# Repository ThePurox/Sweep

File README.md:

# Sweep
<!--
           ___                        ___
      ___ |   | ___ ___      ___ ___ |   | ___
 ___ |   |`___`|   |   |    |   |   |`___`|   | ___
|   |`___`|   |`___`___`    `___`___`|   |`___`|   |
`___`|   |`___`|   |   |    |   |   |`___`|   |`___`
|   |`___`|   |`___`___`    `___`___`|   |`___`|   |
`___`|   |`___`|   |   |    |   |   |`___`|   |`___`
|   |`___`     `___`___`    `___`___`     `___`|   |
`___`           ___ ___      ___ ___           `___`
               |   |   |    |   |   |
               `___`___`    `___`___`
-->
>    
> <sub>Bluetooth Sweep 2 + MBK Legend Keycaps</sub>

<span>

</span>

## What is sweep?

Sweep is a version of the more fabulous [Ferris](https://github.com/pierrechevalier83/ferris) by [Pierre Chevalier](https://github.com/pierrechevalier83/) that uses a daughter board like a promicro, elite-c, bit-c, nice!nano etc. instead of using onboard components.

## What are the different types?

⭐ Sweep 2 - Recommended Choc v1 board with all the features.  
⭕ Sweep Half Swept - Same as Sweep 2, but with a reversible pro-micro footprint.  
⭕ Sweep Bling MX - An MX only Sweep that features Kailh's hotswap sockets and a stacked case.  
⭕ Sweep Bling LP - A Choc v1 only Sweep that features Kailh's hotswap sockets.  
⭕ Sweep High - Same as the Sweep 2, but trades choc spacing for compatibility with more switches and keycaps.  
⭕ Sweep High M - A soldered MX only Sweep, with a reversible PCB design.  
⭕ Sweep Mini - The only version that supports Choc minis.  
⭕ Sweep ULP - A version for the Cherry Ultra low profile switches.  

| Device | On/Off Switch<sup>[1]</sup> | Reversible PCB<sup>[2]</sup> | Choc V1 | Choc V2 | Choc Mini | MX & Alps | Cherry ULP | Choc Spacing<sup>[3]</sup> | Tenting<sup>[4]</sup> | Hot Swap |
| :--- | :---: | :---: | :---: | :---: | :---: | :---: | :---: | :---: | :---: | :---: |
| Sweep2.x          | ✔ |   | ✔ |   |   |   |   | ✔ | ✔ | Mill-Max (optional) |
| Sweep Bling LP    | ✔ |   | ✔ |   |   |   |   | ✔ | ✔ | Kailh (required) |
| Sweep Bling MX    | ✔ | ✔ |   |   |   | ⚠<br/><sup>[5]</sup> |   |   | ✔ | Kailh (required) |
| Sweep High        | ✔ |   | ✔ | ✔ |   | ✔ |   |   | ✔ |
| Sweep High M      | ✔ | ✔ |   |   |   | MX|   |   | ✔ |   |
| Sweep Half Swept  | ✔ | ✔ | ✔ |   |   |   |   | ✔ | ✔ | Mill-Max (optional) |
| Sweep Mini        |   | ✔ |   |   | ✔ |   |   | ✔ |   |
| Sweep ULP         | ✔ |   |   |   |   |   | ✔ | ✔ |   |

> Note: All versions support bluetooth with Nice!Nano

*<sup>[1]</sup> An on/off switch is recommended for bluetooth builds.*  
*<sup>[2]</sup> With a reversible PCB it's easier to make mistakes during assembly, but it allows you to purchase less boards.*  
*<sup>[3]</sup> Choc spaced boards have the switches in a tighter grid. This provides a better final look but is only compatible with some choc keycaps. (e.g. MBK)*  
*<sup>[4]</sup> Supports splitkb's [tenting puck.](https://splitkb.com/products/tenting-puck?_pos=1&_psq=tenting%20&_ss=e&_v=1.0)*  
*<sup>[5]</sup> MX + kailh hotswap ONLY. Alps are NOT supported.*  

## Components list

To build and use a Sweep you will need:

* 1x PCB Kit
* 2x promicro compatible boards or 2 nice!nanos.
* 34 switches of a compatible type (refer to the compatibility table)
* 34 keycaps
* 2x reset switches (optional; [B3U-1000P(M)](https://github.com/davidphilipbarr/Sweep/issues/20))
* Some little rubber feet/bumpers
* 2x power switches (optional if supported; MSK 12C02)
* 1x TRRS (not TRS!) cable (wired build only)
* 2x TRRS Jack [PJ-320A] (wired build only)
* 1 USB Cable (depends on your micro-controller choice)

## How do I make this thing?

## Firmware

The firmware can be found [with the Ferris  firmware as part of QMK](https://github.com/qmk/qmk_firmware/tree/master/keyboards/ferris/sweep).

Firmware for zmk and bluemicro_ble is called ["Cradio"](https://zmk.dev/docs/hardware/).

## Who made this?

* [Pierre Chevalier](https://github.com/pierrechevalier83)
* [David Barr](https://github.com/davidphilipbarr)
* [Ibnu Daru Aji](https://github.com/ibnuda/)
* [Duccio](https://github.com/duckyb)

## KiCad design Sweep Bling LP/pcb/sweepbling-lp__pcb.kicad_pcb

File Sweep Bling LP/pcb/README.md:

# Sweep Bling LP

This is a kailh hotswap version of the Sweep v2.

This is for choc V2 not compatible with choc v1!!!

## Ordering The PCB

To order the PCB the following settings are recommended<sup>1,2</sup>: 

|Detail|Value|
|---|---|
|Gerber file|`sweepbling-lp__pcb-gerber.zip`|
|Base material|FR-4|
|Layers|2|
|Dimension|216.9mm x 86.9mm|
|Different design|2|
|Delivery format|Panel by customer|
|PCB thickness|1.6mm|
|PCB color|(Personal preference)|
|Silkscreen|(Personal preference)|
|Surface finish|(Personal preference)|
|Outer copper weight|1oz|
|Gold Fingers|No|
|Confirm production file|No|
|Castellated holes|No|
|Remove order number|Yes|

1: Settings are for [JLCPCB](https://jlcpcb.com/), but could work for other manufacturers.

2: Settings are taken from [Kyek's video guide](https://www.youtube.com/watch?v=fBPu7AyDtkM&t=17s).

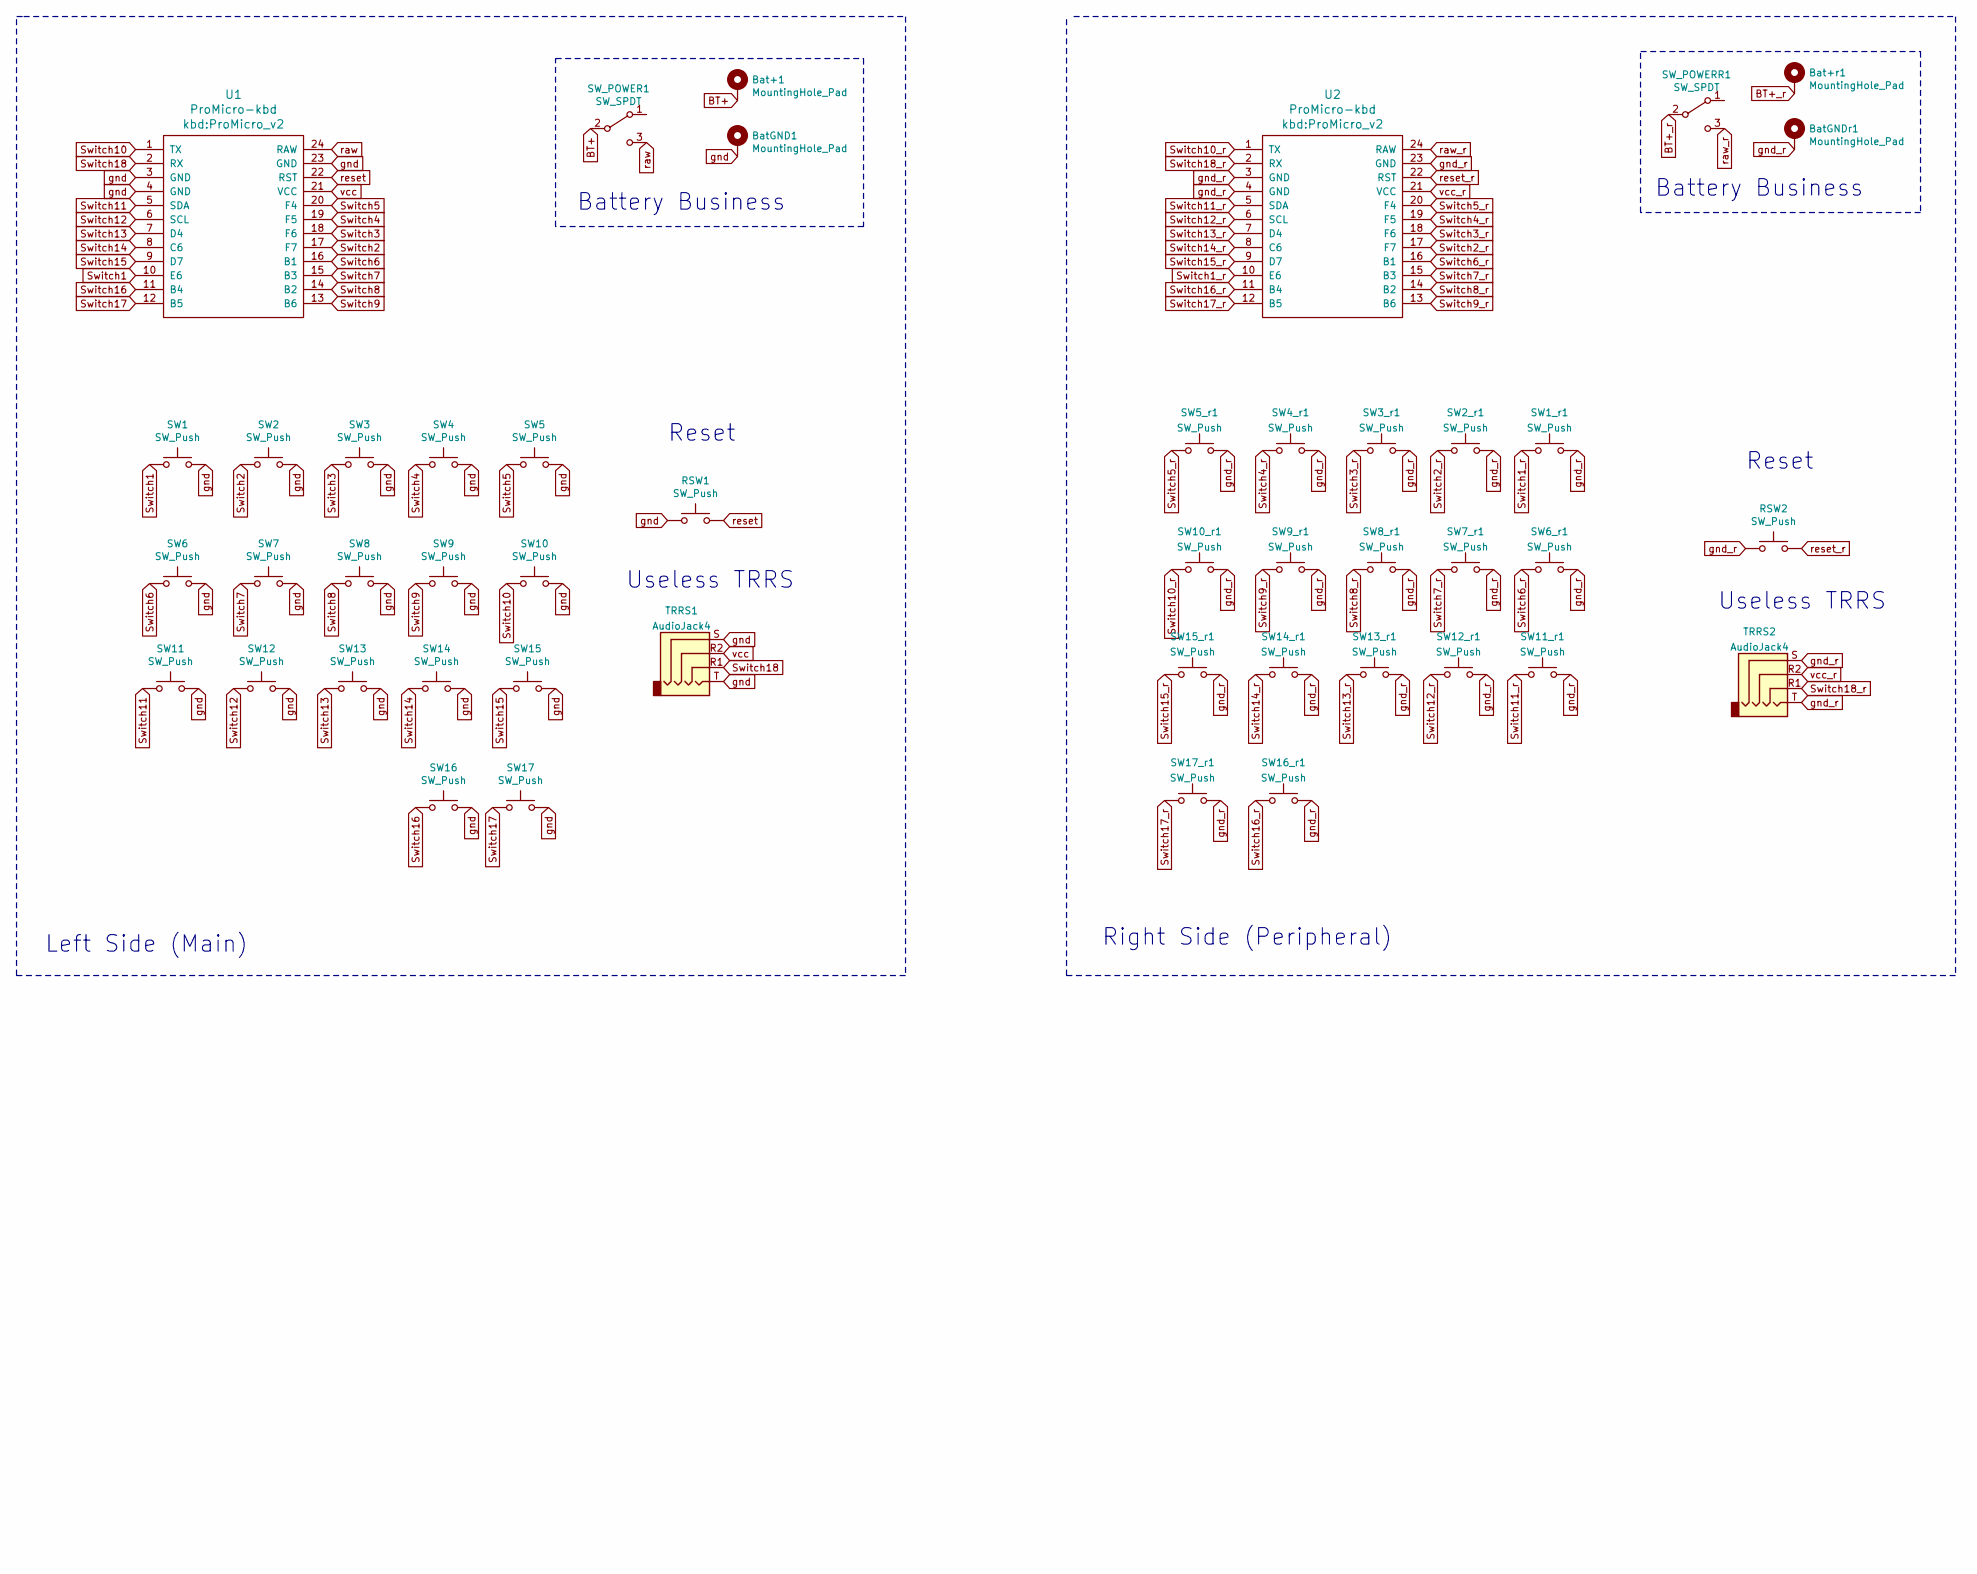
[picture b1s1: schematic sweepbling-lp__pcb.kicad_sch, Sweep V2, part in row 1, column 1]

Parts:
Bat+1: MountingHole_Pad; 1pin_conn
Bat+r1: MountingHole_Pad; 1pin_conn
BatGND1: MountingHole_Pad; 1pin_conn
BatGNDr1: MountingHole_Pad; 1pin_conn
RSW1, RSW2: SW_Push; ResetSW
SW1, SW1_r1, SW2, SW2_r1, SW3, SW3_r1, SW4, SW4_r1, SW5, SW5_r1, SW6, SW6_r1, SW7, SW7_r1, SW8, SW8_r1, SW9, SW9_r1, SW10, SW10_r1, SW11, SW11_r1, SW12, SW12_r1, SW13, SW13_r1, SW14, SW14_r1, SW15, SW15_r1, SW16, SW16_r1, SW17, SW17_r1: SW_Push; SW_PG1350_rev_DPB
SW_POWER1: SW_SPDT; SPDT_C128955
SW_POWERR1: SW_SPDT; SPDT_C128955
TRRS1, TRRS2: AudioJack4
U1, U2: ProMicro-kbd; ProMicro_v2

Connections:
BT+: Bat+1.1 (1_1), SW_POWER1.2 (B)
BT+_r: Bat+r1.1 (1_1), SW_POWERR1.2 (B)
Switch1: SW1.2, U1.10 (E6)
Switch1_r: SW1_r1.2, U2.10 (E6)
Switch2: SW2.2, U1.17 (F7)
Switch2_r: SW2_r1.2, U2.17 (F7)
Switch3: SW3.2, U1.18 (F6)
Switch3_r: SW3_r1.2, U2.18 (F6)
Switch4: SW4.2, U1.19 (F5)
Switch4_r: SW4_r1.2, U2.19 (F5)
Switch5: SW5.2, U1.20 (F4)
Switch5_r: SW5_r1.2, U2.20 (F4)
Switch6: SW6.2, U1.16 (B1)
Switch6_r: SW6_r1.2, U2.16 (B1)
Switch7: SW7.2, U1.15 (B3)
Switch7_r: SW7_r1.2, U2.15 (B3)
Switch8: SW8.2, U1.14 (B2)
Switch8_r: SW8_r1.2, U2.14 (B2)
Switch9: SW9.2, U1.13 (B6)
Switch9_r: SW9_r1.2, U2.13 (B6)
Switch10: SW10.2, U1.1 (TX)
Switch10_r: SW10_r1.2, U2.1 (TX)
Switch11: SW11.2, U1.5 (SDA)
Switch11_r: SW11_r1.2, U2.5 (SDA)
Switch12: SW12.2, U1.6 (SCL)
Switch12_r: SW12_r1.2, U2.6 (SCL)
Switch13: SW13.2, U1.7 (D4)
Switch13_r: SW13_r1.2, U2.7 (D4)
Switch14: SW14.2, U1.8 (C6)
Switch14_r: SW14_r1.2, U2.8 (C6)
Switch15: SW15.2, U1.9 (D7)
Switch15_r: SW15_r1.2, U2.9 (D7)
Switch16: SW16.2, U1.11 (B4)
Switch16_r: SW16_r1.2, U2.11 (B4)
Switch17: SW17.2, U1.12 (B5)
Switch17_r: SW17_r1.2, U2.12 (B5)
Switch18: TRRS1.R1, U1.2 (RX)
Switch18_r: TRRS2.R1, U2.2 (RX)
gnd: BatGND1.1 (1_1), RSW1.1, SW1.1, SW2.1, SW3.1, SW4.1, SW5.1, SW6.1, SW7.1, SW8.1, SW9.1, SW10.1, SW11.1, SW12.1, SW13.1, SW14.1, SW15.1, SW16.1, SW17.1, TRRS1.S, TRRS1.T, U1.3 (GND), U1.4 (GND), U1.23 (GND)
gnd_r: BatGNDr1.1 (1_1), RSW2.1, SW1_r1.1, SW2_r1.1, SW3_r1.1, SW4_r1.1, SW5_r1.1, SW6_r1.1, SW7_r1.1, SW8_r1.1, SW9_r1.1, SW10_r1.1, SW11_r1.1, SW12_r1.1, SW13_r1.1, SW14_r1.1, SW15_r1.1, SW16_r1.1, SW17_r1.1, TRRS2.S, TRRS2.T, U2.3 (GND), U2.4 (GND), U2.23 (GND)
raw: SW_POWER1.3 (C), U1.24 (RAW)
raw_r: SW_POWERR1.3 (C), U2.24 (RAW)
reset: RSW1.2, U1.22 (RST)
reset_r: RSW2.2, U2.22 (RST)
vcc: TRRS1.R2, U1.21 (VCC)
vcc_r: TRRS2.R2, U2.21 (VCC)

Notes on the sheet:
Battery Business
Useless TRRS
Reset
Left Side (Main)
Right Side (Peripheral)

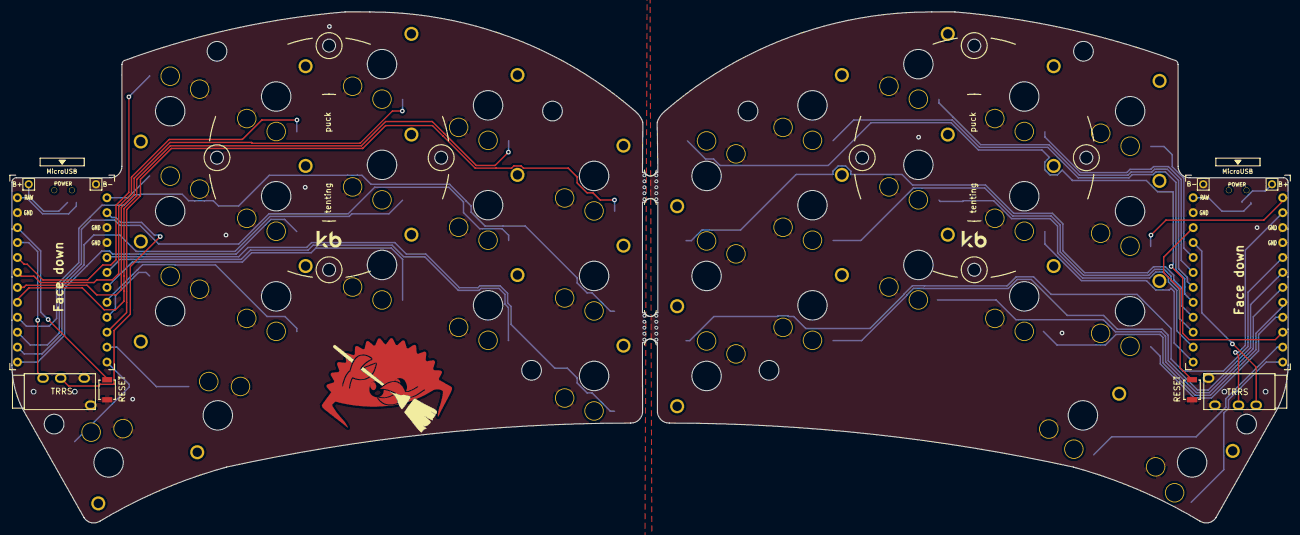
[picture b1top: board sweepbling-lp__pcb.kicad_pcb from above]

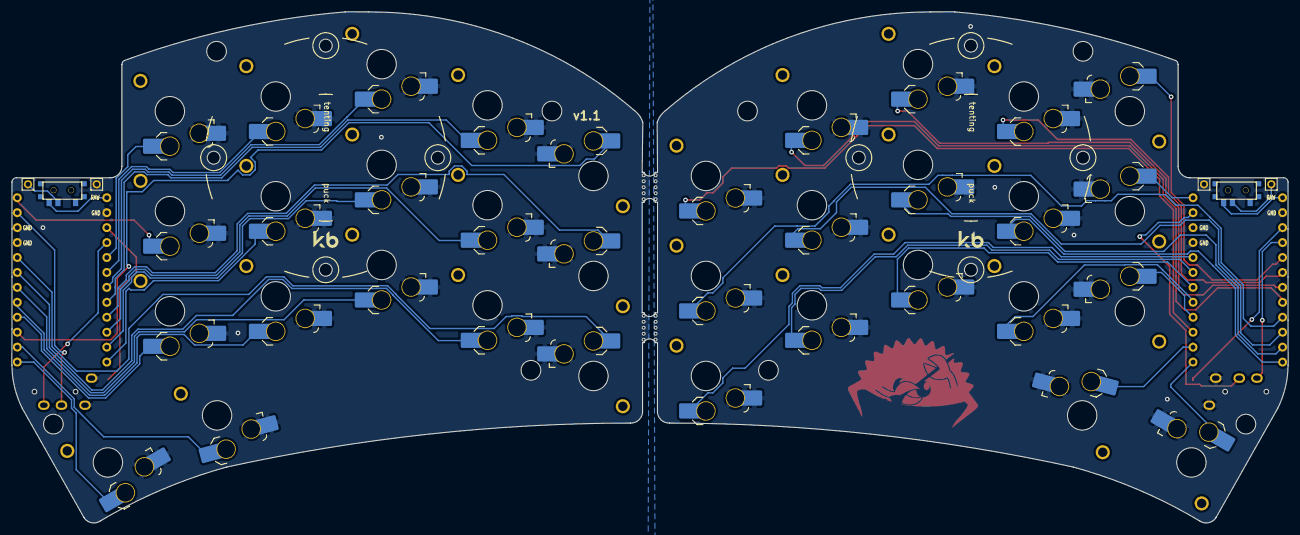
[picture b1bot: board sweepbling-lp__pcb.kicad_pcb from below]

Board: 2 copper layers, 216.9 x 86.9 mm, 51 parts (36 on the bottom side), 46 nets.

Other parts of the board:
REF_PUCK_R: Tenting Puck; Tenting_Puck2_no_pads
SweepLogo: LOGO; ferris_broom
e: Tenting Puck; Tenting_Puck2_no_pads
mouse-bite-2mm-slot1, mouse-bite-2mm-slot2: VAL**; mouse-bite-5mm-slot-with-space-for-track

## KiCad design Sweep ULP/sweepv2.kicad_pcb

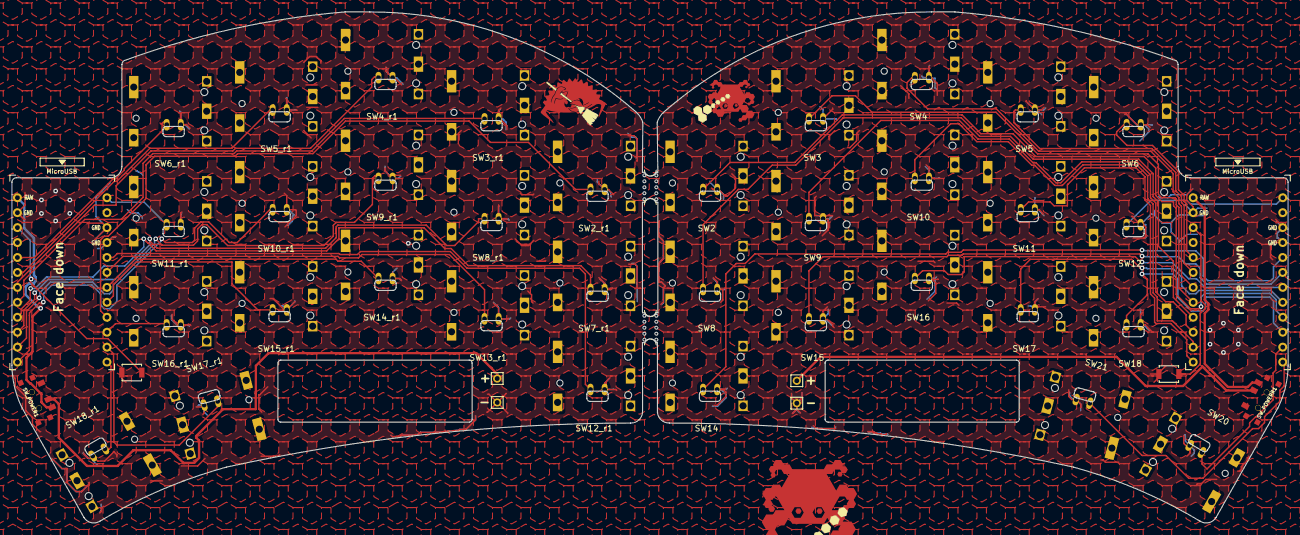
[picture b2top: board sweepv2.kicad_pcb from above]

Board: 2 copper layers, 216.9 x 86.9 mm, 46 parts (0 on the bottom side), 41 nets.

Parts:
Bat+1: MountingHole_Pad; 1pin_conn
Bat+r1: MountingHole_Pad; 1pin_conn
BatGND1, BatGND4: MountingHole_Pad; 1pin_conn
RSW1, RSW2: SW_Push; SW_SPST_B3U-1000P
SW2, SW2_r1, SW3, SW3_r1, SW4, SW4_r1, SW5, SW5_r1, SW6, SW6_r1, SW7_r1, SW8, SW8_r1, SW9, SW9_r1, SW10, SW10_r1, SW11, SW11_r1, SW12, SW12_r1, SW13_r1, SW14, SW14_r1, SW15, SW15_r1, SW16, SW16_r1, SW17, SW17_r1, SW18, SW18_r1, SW20, SW21: SW_Push; Cherry_ULP_TH_CUT_3D
SW_POWER1: SW_SPDT; SPDT_C128955
SW_POWERR1: SW_SPDT; SPDT_C128955
U1, U2: ProMicro-kbd; ProMicro_v3_min
mouse-bite-2mm-slot, mouse-bite-2mm-slot#2: VAL**; mouse-bite-5mm-slot-with-space-for-track

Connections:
BT+: Bat+1.1, SW_POWER1.2 (B)
BT+_r: Bat+r1.1, SW_POWERR1.2 (B)
Switch1: SW2.1, U1.9 (D7)
Switch1_r: SW2_r1.1, U2.9 (D7)
Switch2: SW3.1, U1.17 (F7)
Switch2_r: SW3_r1.1, U2.17 (F7)
Switch3: SW4.1, U1.18 (F6)
Switch3_r: SW4_r1.1, U2.18 (F6)
Switch4: SW5.1, U1.19 (F5)
Switch4_r: SW5_r1.1, U2.19 (F5)
Switch5: SW6.1, U1.20 (F4)
Switch5_r: SW6_r1.1, U2.20 (F4)
Switch6: SW8.1, U1.16 (B1)
Switch6_r: SW7_r1.1, U2.16 (B1)
Switch7: SW9.1, U1.15 (B3)
Switch7_r: SW8_r1.1, U2.15 (B3)
Switch8: SW10.1, U1.14 (B2)
Switch8_r: SW9_r1.1, U2.14 (B2)
Switch9: SW11.1, U1.13 (B6)
Switch9_r: SW10_r1.1, U2.13 (B6)
Switch10: SW12.1, U1.1 (TX)
Switch10_r: SW11_r1.1, U2.1 (TX)
Switch11: SW14.1, U1.5 (SDA)
Switch11_r: SW12_r1.1, U2.5 (SDA)
Switch12: SW15.1, U1.6 (SCL)
Switch12_r: SW13_r1.1, U2.6 (SCL)
Switch13: SW16.1, U1.7 (D4)
Switch13_r: SW14_r1.1, U2.7 (D4)
Switch14: SW17.1, U1.8 (C6)
Switch14_r: SW15_r1.1, U2.8 (C6)
Switch15: SW18.1, U1.10 (E6)
Switch15_r: SW16_r1.1, U2.10 (E6)
Switch16: SW20.1, U1.11 (B4)
Switch16_r: SW17_r1.1, U2.11 (B4)
Switch17: SW21.1, U1.12 (B5)
Switch17_r: SW18_r1.1, U2.12 (B5)
gnd: BatGND1.1, BatGND4.1, RSW1.1, RSW2.1, SW2.2, SW2_r1.2, SW3.2, SW3_r1.2, SW4.2, SW4_r1.2, SW5.2, SW5_r1.2, SW6.2, SW6_r1.2, SW7_r1.2, SW8.2, SW8_r1.2, SW9.2, SW9_r1.2, SW10.2, SW10_r1.2, SW11.2, SW11_r1.2, SW12.2, SW12_r1.2, SW13_r1.2, SW14.2, SW14_r1.2, SW15.2, SW15_r1.2, SW16.2, SW16_r1.2, SW17.2, SW17_r1.2, SW18.2, SW18_r1.2, SW20.2, SW21.2, U1.3 (GND), U1.4 (GND), U1.23 (GND), U2.3 (GND), U2.4 (GND), U2.23 (GND)
raw: SW_POWER1.3 (C), SW_POWERR1.3 (C), U1.24 (RAW), U2.24 (RAW)
reset: RSW1.2, U1.22 (RST)
reset_r: RSW2.2, U2.22 (RST)
vcc: U1.21 (VCC), U2.21 (VCC)

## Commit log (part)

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2025-11-04 added ultra low profile Sweep, aka Swulp
2025-11-04 hexed ground and added crab
2025-11-08 moved batteries and switches around
2025-11-08 removed annoying silk
2025-11-08 updated local readme and added gerbers
